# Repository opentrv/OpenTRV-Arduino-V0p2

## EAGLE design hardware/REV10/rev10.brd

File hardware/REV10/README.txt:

REV 10 is RFM23B and phototransistor and TMP112 and GSM card and optional mains power and optional relay.
Dual purpose for temp sensor deployment and as a general dumb sensor radio relay over GSM.

See requirements doc: https://docs.google.com/document/d/1RM6_tcC0Uajx6D2YfQV9GoQAOvQpk6TpT7khfn3ezBs/edit?usp=sharing

Note ITEADstudio .dru and .cam files downloaded from their site AND NOT COVERED BY OUR APACHE LICENCE
though ITEADstudio would probably be happy for you to use their service like we did!

Component-ordering document: https://docs.google.com/spreadsheets/d/10yWM68cfkmaEVJMniHg1qRwaJqgsrZ1O5jhQIcJ3FMg/edit#gid=0

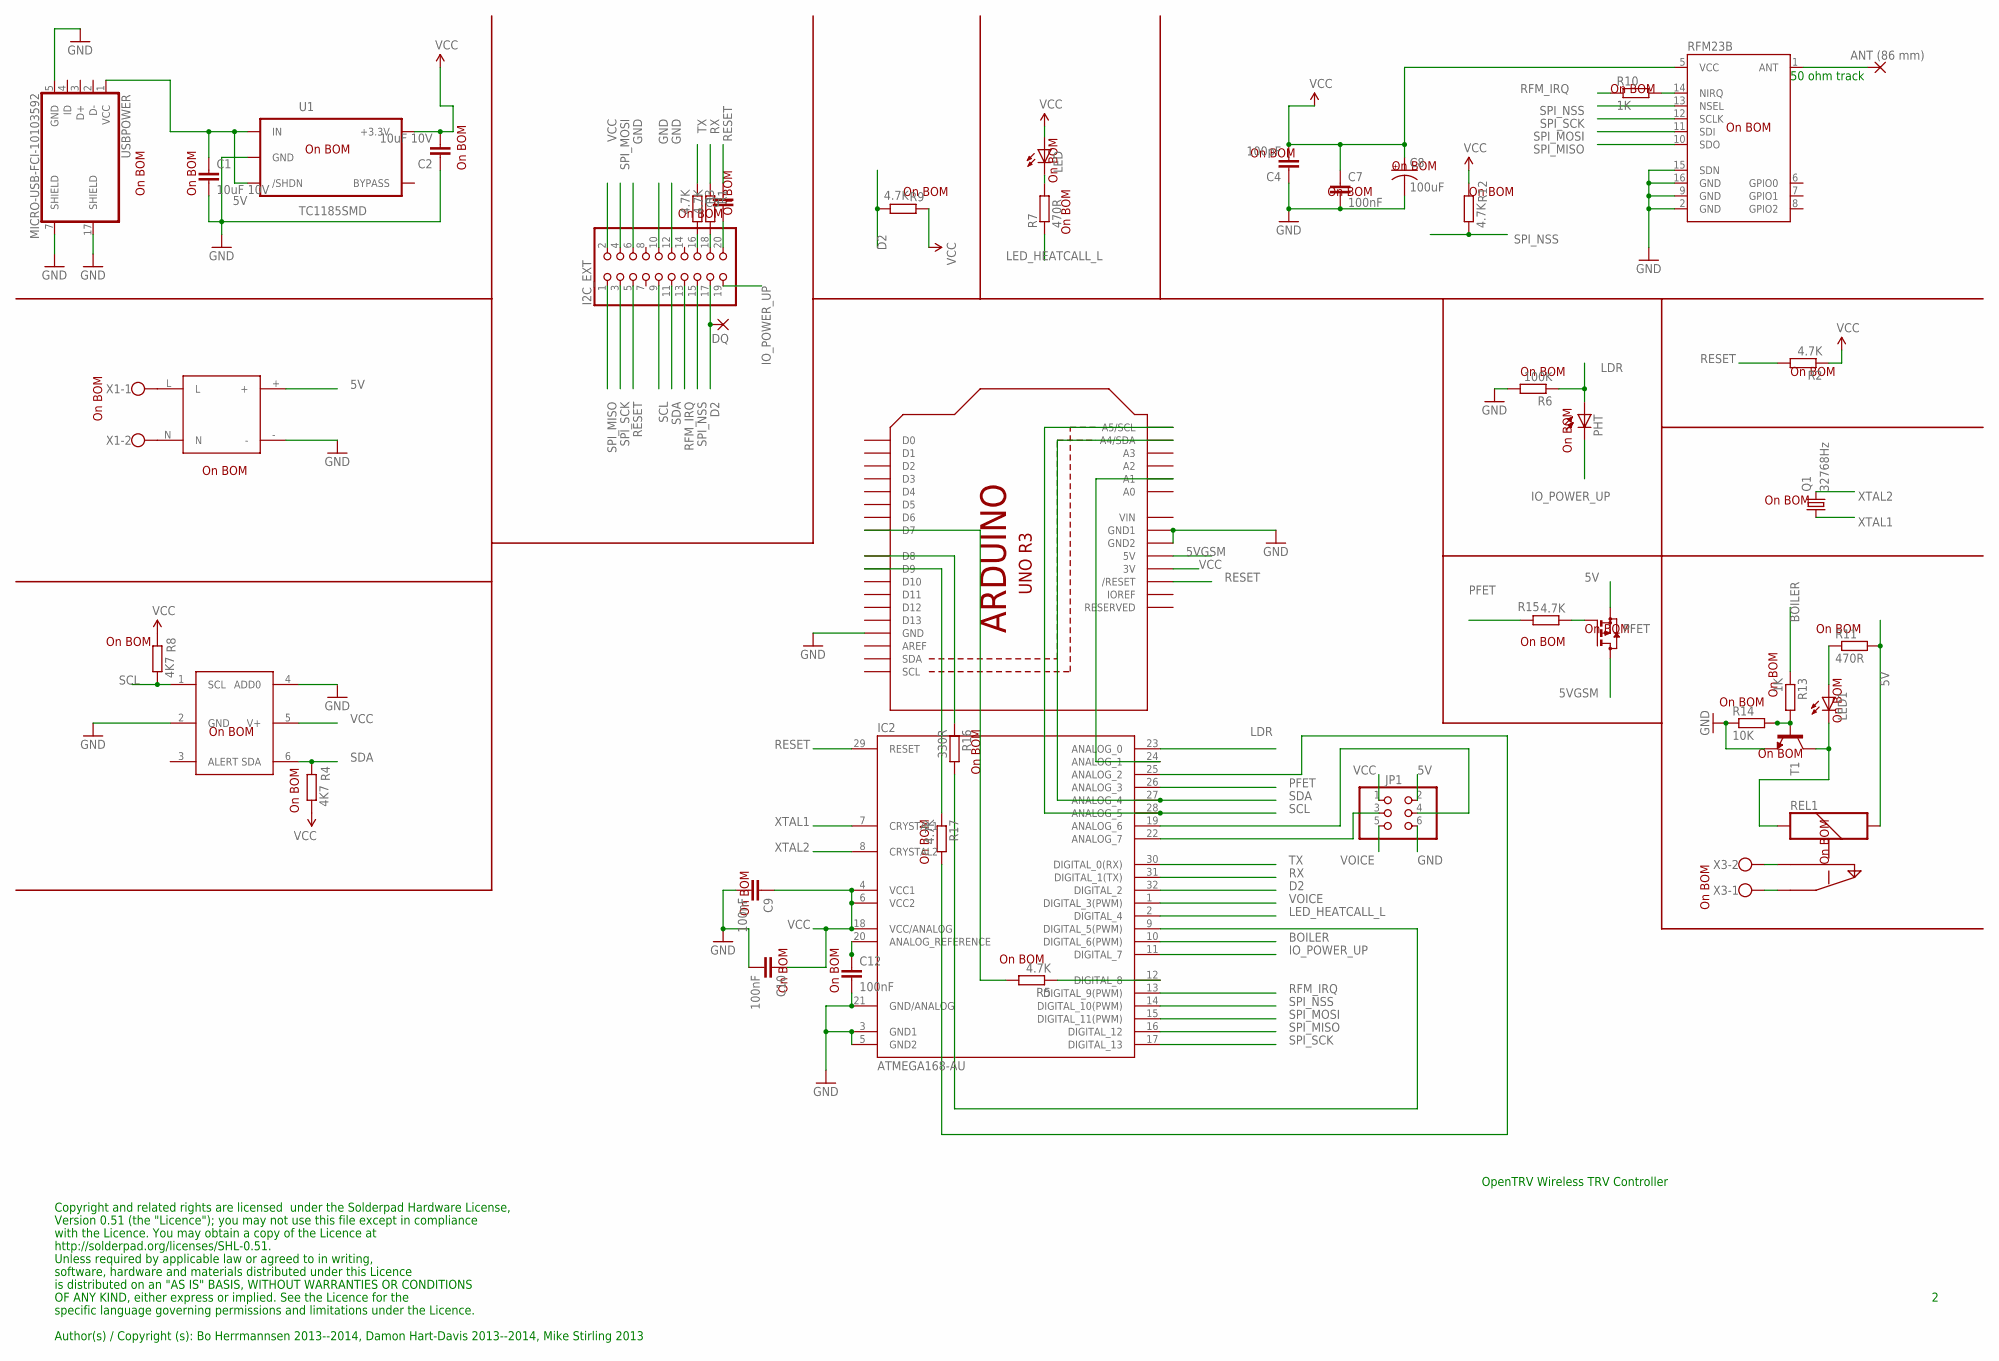
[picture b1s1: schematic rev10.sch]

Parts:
ANT1: ANT (86 mm); 2,15/1,0
C1, C2: 10uF 10V; C0603
C4: 100pF; C0603
C5, C7, C9, C10, C12: 100nF; C0603
C8: 100uF; EIA3216
DQ: 2,15/1,0
I2C_EXT: PINHD-2X10; 2X10
IC2: ATMEGA168-AU; TQFP32-08
JP1: PINHD-2X3; 2X03
LED, LED1: LEDCHIP-LED0603; CHIP-LED0603
PFET: BSS84; SOT23
PHT: BPX65
PSU: VTX-214-010-205
Q1: 32768Hz; MC-306
R1, R2, R3, R5, R9, R12, R15, R17: 4.7K; R0603
R4, R8: 4K7; R0603
R6: 100K; R0603
R7, R11: 470R; R0603
R10, R13: 1K; R0603
R14: 10K; R0603
R16: 330R; R0603
REL1: OJE-SS-103HM
RFM23B: RFM23B; RFM23-XXX-S1
T1: -NPN-SOT23-EBC; SOT23-EBC
TMP112: TMP1; TMP112
U1: TC1185SMD; TC1185
U$3: ARDUINO
USBPOWER: MICRO-USB-FCI-10103592
X1, X3: W237-102

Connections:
5V: C1.1, JP1.2, PFET.2 (S), PSU.+, R11.2, REL1.S2, U1.1 (IN), U1.3 (/SHDN), USBPOWER.1 (VCC)
5VGSM: PFET.3 (D), U$3.5V
BOILER: IC2.10 (DIGITAL_6(PWM)), R13.1
D2: DQ.1, I2C_EXT.17, IC2.32 (DIGITAL_2), R9.1
GND: C1.2, C2.1, C4.1, C7.2, C8.C (-), C9.2, C10.2, C12.2, I2C_EXT.6, I2C_EXT.10, I2C_EXT.12, IC2.3 (GND1), IC2.5 (GND2), IC2.21 (GND/ANALOG), JP1.6, PSU.-, R6.2, R14.1, RFM23B.2 (GND), RFM23B.9 (GND), RFM23B.15 (SDN), RFM23B.16 (GND), T1.E, TMP112.2 (GND), TMP112.4 (ADD0), U1.2 (GND), U$3.GND, U$3.GND1, U$3.GND2, USBPOWER.5 (GND), USBPOWER.7 (SHIELD), USBPOWER.17 (SHIELD)
IO_POWER_UP: I2C_EXT.19, IC2.11 (DIGITAL_7), PHT.K (C)
LDR: IC2.23 (ANALOG_0), PHT.A, R6.1
LED_HEATCALL_L: IC2.2 (DIGITAL_4), R7.1
unnamed: IC2.19 (ANALOG_6), JP1.4
unnamed: IC2.12 (DIGITAL_8), R5.1
unnamed: PSU.N, X1.2
unnamed: IC2.22 (ANALOG_7), JP1.3
unnamed: C12.1, IC2.20 (ANALOG_REFERENCE)
unnamed: R10.2, RFM23B.14 (NIRQ)
unnamed: PSU.L, X1.1
unnamed: IC2.25 (ANALOG_2), R17.2
unnamed: R13.2, R14.2, T1.B
unnamed: LED.C, R7.2
unnamed: LED1.C, REL1.S1, T1.C
unnamed: IC2.24 (ANALOG_1), U$3.A1
unnamed: LED1.A, R11.1
unnamed: PFET.1 (G), R15.1
unnamed: R5.2, U$3.D7
unnamed: IC2.9 (DIGITAL_5(PWM)), R16.2
unnamed: REL1.C, X3.1
unnamed: REL1.S, X3.2
unnamed: I2C_EXT.18, R1.2
unnamed: I2C_EXT.16, R3.2
unnamed: C5.2, I2C_EXT.20
unnamed: R17.1, U$3.D9
unnamed: ANT1.1, RFM23B.1 (ANT)
unnamed: R16.1, U$3.D8
PFET: IC2.26 (ANALOG_3), R15.2
RESET: C5.1, I2C_EXT.5, IC2.29 (RESET), R2.2, U$3.RESET (/RESET)
RFM_IRQ: I2C_EXT.13, IC2.13 (DIGITAL_9(PWM)), R10.1
RX: IC2.31 (DIGITAL_1(TX)), R1.1
SCL: I2C_EXT.9, IC2.28 (ANALOG_5), R8.1, TMP112.1 (SCL), U$3.A5 (A5/SCL)
SDA: I2C_EXT.11, IC2.27 (ANALOG_4), R4.2, TMP112.6 (SDA), U$3.A4 (A4/SDA)
SPI_MISO: I2C_EXT.1, IC2.16 (DIGITAL_12), RFM23B.10 (SDO)
SPI_MOSI: I2C_EXT.4, IC2.15 (DIGITAL_11(PWM)), RFM23B.11 (SDI)
SPI_NSS: I2C_EXT.15, IC2.14 (DIGITAL_10(PWM)), R12.1, RFM23B.13 (NSEL)
SPI_SCK: I2C_EXT.3, IC2.17 (DIGITAL_13), RFM23B.12 (SCLK)
TX: IC2.30 (DIGITAL_0(RX)), R3.1
VCC: C2.2, C4.2, C7.1, C8.A (+), C9.1, C10.1, I2C_EXT.2, IC2.4 (VCC1), IC2.6 (VCC2), IC2.18 (VCC/ANALOG), JP1.1, LED.A, R2.1, R4.1, R8.2, R9.2, R12.2, RFM23B.5 (VCC), TMP112.5 (V+), U1.5 (+3.3V), U$3.3V
VIN: U$3.VIN
VOICE: IC2.1 (DIGITAL_3(PWM)), JP1.5
XTAL1: IC2.7 (CRYSTAL1), Q1.1
XTAL2: IC2.8 (CRYSTAL2), Q1.4 (2)

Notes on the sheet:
Copyright and related rights are licensed under the Solderpad Hardware License,
Version 0.51 (the "Licence"); you may not use this file except in compliance
with the Licence. You may obtain a copy of the Licence at
http://solderpad.org/licenses/SHL-0.51.
Unless required by applicable law or agreed to in writing,
software, hardware and materials distributed under this Licence
is distributed on an "AS IS" BASIS, WITHOUT WARRANTIES OR CONDITIONS
Author(s) / Copyright (s): Bo Herrmannsen 2013--2014, Damon Hart-Davis 2013--2014, Mike Stirling 2013
OpenTRV Wireless TRV Controller
OF ANY KIND, either express or implied. See the Licence for the
specific language governing permissions and limitations under the Licence.
50 ohm track
On BOM

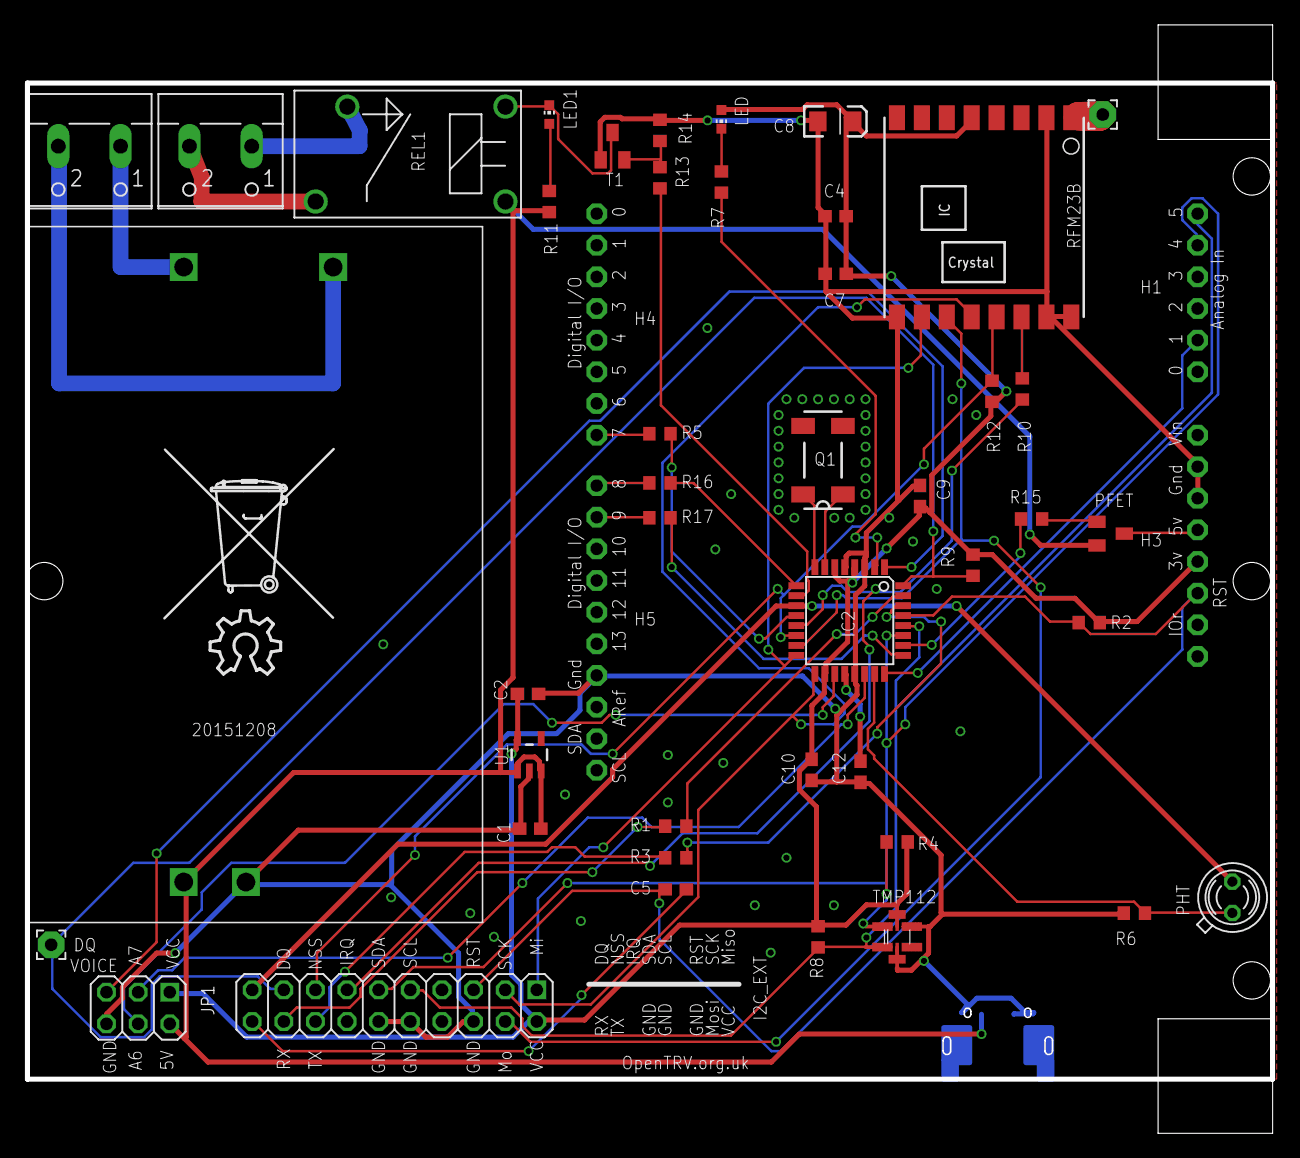
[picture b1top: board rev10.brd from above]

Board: 2 copper layers, 100.0 x 80.0 mm, 48 parts (1 on the bottom side), 47 nets.

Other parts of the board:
U$1: OSHW_10X200_NOTEXT
U$2: TONNE

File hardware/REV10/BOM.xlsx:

# of boards ttl | 100.0 |  |  | GREEN MEANS OK | RED MEANS OUT OF STOCK
Quantity per board | Need to order | Min order | Unit price | Line Total | Seller Stock No | Manufacturer | Manufacturer Part. No. | Description | Legend | Supplier | Direct Link
1.0 | 100 | 5.0 | 0.342 | 34.2 | 714-2334 | FCI | 10103592-0001LF | Micro USB socket | USBPOWER | RS Components | http://uk.rs-online.com/web/p/micro-usb-connectors/7142334/
1.0 | 100 | 10.0 | 0.241 | 24.1 | 628-3661 | Microchip | TC1185-3.3VCT713 | 3.3V Regulator | U1 | RS Components | http://uk.rs-online.com/web/p/low-dropout-voltage-regulators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
2.0 | 200 | 50.0 | 0.103 | 20.6 | 741-4434 | TDK | C1608X5R0J106M080AB | 10 uF | C1, C2 | RS Components | http://uk.rs-online.com/web/p/ceramic-multilayer-capacitors/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
1.0 | 100 | 50.0 | 0.027 | 2.7 | 213-2531 | TE Connectivity | CRG0603F100K | 100Kohm | R6 | RS Components | http://uk.rs-online.com/web/p/surface-mount-fixed-resistors/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
10.0 | 1000 | 50.0 | 0.028 | 28 | 213-2367 | TE Connectivity | CRG0603F4K7 | 4.7Kohm | R4, R8, R1, R3, R9, R12, R2, R17, R5, R15 | RS Components | http://uk.rs-online.com/web/p/surface-mount-fixed-resistors/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
2.0 | 200 | 50.0 | 0.028 | 5.6 | 213-2222 | TE Connectivity | CRG0603F470R | 470ohm | R7, R11 | RS Components | http://uk.rs-online.com/web/p/surface-mount-fixed-resistors/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
2.0 | 200 | 50.0 | 0.006 | 1.2 | 213-2266 | TE Connectivity | CRG0603F1K0 | 1Kohm | R10, R13 | RS Components | http://uk.rs-online.com/web/p/surface-mount-fixed-resistors/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
1.0 | 100 | 50.0 | 0.008 | 0.8 | 679-0226 | Vishay | CRCW0603330RFKEA | 330ohm | R16 | RS Components | http://uk.rs-online.com/web/p/surface-mount-fixed-resistors/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
1.0 | 100 | 50.0 | 0.011 | 1.1 | 213-2418 | TE Connectivity | CRG0603F10K | 10Kohm | R14 | RS Components | http://uk.rs-online.com/web/p/surface-mount-fixed-resistors/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
5.0 | 500 | 25.0 | 0.022 | 11 | 264-4630 | Kemet | C0603C104K4RAC | 100nF | C5, C9, C10, C12, C7 | RS Components | http://uk.rs-online.com/web/p/ceramic-multilayer-capacitors/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
1.0 | 100 | 50.0 | 0.026 | 2.6 | 464-6391 | AVX | 06035A101JAT2A | 100pF | C4 | RS Components | http://uk.rs-online.com/web/p/ceramic-multilayer-capacitors/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
1.0 | 100 | 10.0 | 0.215 | 21.5 | 885-1897 | Murata | GRM31CD80J107ME39L | 100uF | C8 | RS Components | http://uk.rs-online.com/web/p/ceramic-multilayer-capacitors/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
1.0 | 100 | 5.0 | 0.824 | 82.4 | 667-6120 | EPSON TOYOCOM | MC-306, 32.768kHz, 20ppm, 6pF | Crystal | Q1 | RS Components | http://uk.rs-online.com/web/p/crystal-units/6676120
1.0 | 100 | 1.0 | 1.91 | 191 | 709-8868 | Texas Instruments | TMP112AIDRLT | TMP112 | TMP112 | RS Components | http://uk.rs-online.com/web/p/temperature-humidity-sensors/7098868
2.0 | 200 | 5.0 | 0.191 | 38.2 | 1328308.0 | Vishay | TLMS1000-GS08 | LED RED | LED, LED1 | Farnell | http://uk.farnell.com/vishay/tlms1000-gs08/led-0603-red-4mcd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
1.0 | 100 | 10.0 | 0.293 | 29.3 | 700-0776 | Vishay | TEPT4400 | 60° Visible Light Phototransistor | PHT | RS Components | http://uk.rs-online.com/web/p/phototransistors/7000776/
0.001 | 0.1 | 1000.0 | 11.99 | 1.199 | 712-5320 | RS |  | 84mm* of insulated semi-flexible antenna wire (~0.33sqmm). *Depends on PCB trac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 | ANT | RS Components | http://uk.rs-online.com/web/p/hookup-equipment-wire/7125320
1.0 | 100 | 1.0 | 2.53 | 253 | 696-3092 | Atmel | ATMEGA328P-AU | ATmega328P-AU | IC1 | RS Components | http://uk.rs-online.com/web/p/microcontrollers/6963092/
1.0 | 100 | 1.0 | 3.6 | 360 | RFM23-868-S1 | HopeRF | RFM23-868-S1 | RFM23B | RFM23 | Ideetron | http://www.hoperf.nl/RFM23B
1.0 | 100 | 5.0 | 1.008 | 100.8 | 4681350.0 | Molex | 90122-0767 | Right Angle 14 Pin connector | IC2_EXT | RS Components | http://uk.rs-online.com/web/p/pcb-headers/4681350/
1.0 | 100 | 1.0 | 6.21 | 621 | 84-2192 | Vigortronix | VTX-214-010-105 | 230V AC -> 5V DC Switchmode | PSU | Rapid Online | http://www.rapidonline.com/Electrical-Power/Vigortronix-VTX-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
1.0 | 100 | 1.0 | 0.561 | 56.1 | 1891660.0 | TE Connectivity | OJE-SS-103HM,000 | Relay | Rel1 | Farnell | http://uk.farnell.com/te-connectivity-oeg/oje-ss-103hm-000/r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
1.0 | 100 | 100.0 | 0.062 | 6.2 | 827-0503 | DiodesZetex | DMP3099L-7 | PFET Sot23 | PFET | RS Components | http://uk.rs-online.com/web/p/mosfet-transistors/8270503/
1.0 | 100 | 50.0 | 0.008 | 0.8 | 445-2039 | Infineon | BC848C | NPN Sot23 | T1 | RS Components | http://uk.rs-online.com/web/p/bipolar-transistors/4452039/
2.0 | 200 | 10.0 | 0.413 | 82.6 | 710-0093 | TE Connectivity | 1546216-2 | 2 way screw terminal | X1, X3 | RS Components | http://uk.rs-online.com/web/p/pcb-terminal-blocks/7100093/
1.0 | 100 | 10.0 | 0.346 | 34.6 | 668-9485 | TE Connectivity | 826634-3 | 6 pin header | JP2 | RS Components | http://uk.rs-online.com/web/p/pcb-headers/6689485/
2.0 | 200 | 10.0 | 0.287 | 57.4 | 1593478.0 | Multicomp | 2212BR-08G | 8 pin Arduino receptacle | ?? | Farnell | http://uk.farnell.com/multicomp/2212br-08g/socket-pcb-r-a-1-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
1.0 | 100 | 10.0 | 0.561 | 56.1 | 1593462.0 | Multicomp | 2212S-06SG-85 | 6 pin Arduino receptacle | ?? | Farnell | http://uk.farnell.com/multicomp/2212s-06sg-85/socket-pcb-1-r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
1.0 | 100 | 10.0 | 0.375 | 37.5 | 7991959.0 | Harwin | M20-7821046 | 10 pin Arduino receptacle | ?? | Farnell | http://uk.farnell.com/harwin/m20-7821046/socket-pcb-0-1-10wa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
1.0 | 100 |  |  |  |  |  |  | PCB's |  | ?
1.0 | 100 |  |  |  |  |  |  | SIM900 shield |  | ? | Link??
 |  |  | Total: | 2161.599
 |  |  | Per board | 21.61599
Out of stock
1.0 | 100 | 5.0 | 0.71 | 71 | 749-2059 | Murata | GRM31CR60G107ME39L | 100uF | C8 | RS Components | http://uk.rs-online.com/web/p/ceramic-multilayer-capacitors/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
2.0 | 200 | 100.0 | 0.127 | 25.4 | 888-6029 | Lumex | SML-LX0603SIW-TR | LED RED | LED, LED1 | RS Components | http://uk.rs-online.com/web/p/visible-leds/8886029/

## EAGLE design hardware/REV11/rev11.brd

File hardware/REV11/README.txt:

REV 11 is RFM23B and phototransistor and SHT21, with no UI eg neither buttons nor LEDs.
Light-weight passive sensor, eg for baseline and general monitoring/measurement in homes.
Senses/reports: ambient light, temperature, relative humidity (plus battery voltage and restarts).
Powered by AAA cells to save space, and designed to fit into a relatively discreet small vented plastic case.

Target box: http://m.rapidonline.com/mechanical-fastenings-fixings/low-profile-sensor-case-white-30-3226

(Note: board is smaller than the maximum possible.)

Note ITEADstudio .dru and .cam files downloaded from their site AND NOT COVERED BY OUR APACHE LICENCE
though ITEADstudio would probably be happy for you to use their service like we did!

Component-ordering document: https://docs.google.com/spreadsheets/d/1gsCwtDZDTSBvkgDIGdEZPMJ3iMatSaSa38pdLNWTiDY/edit#gid=0

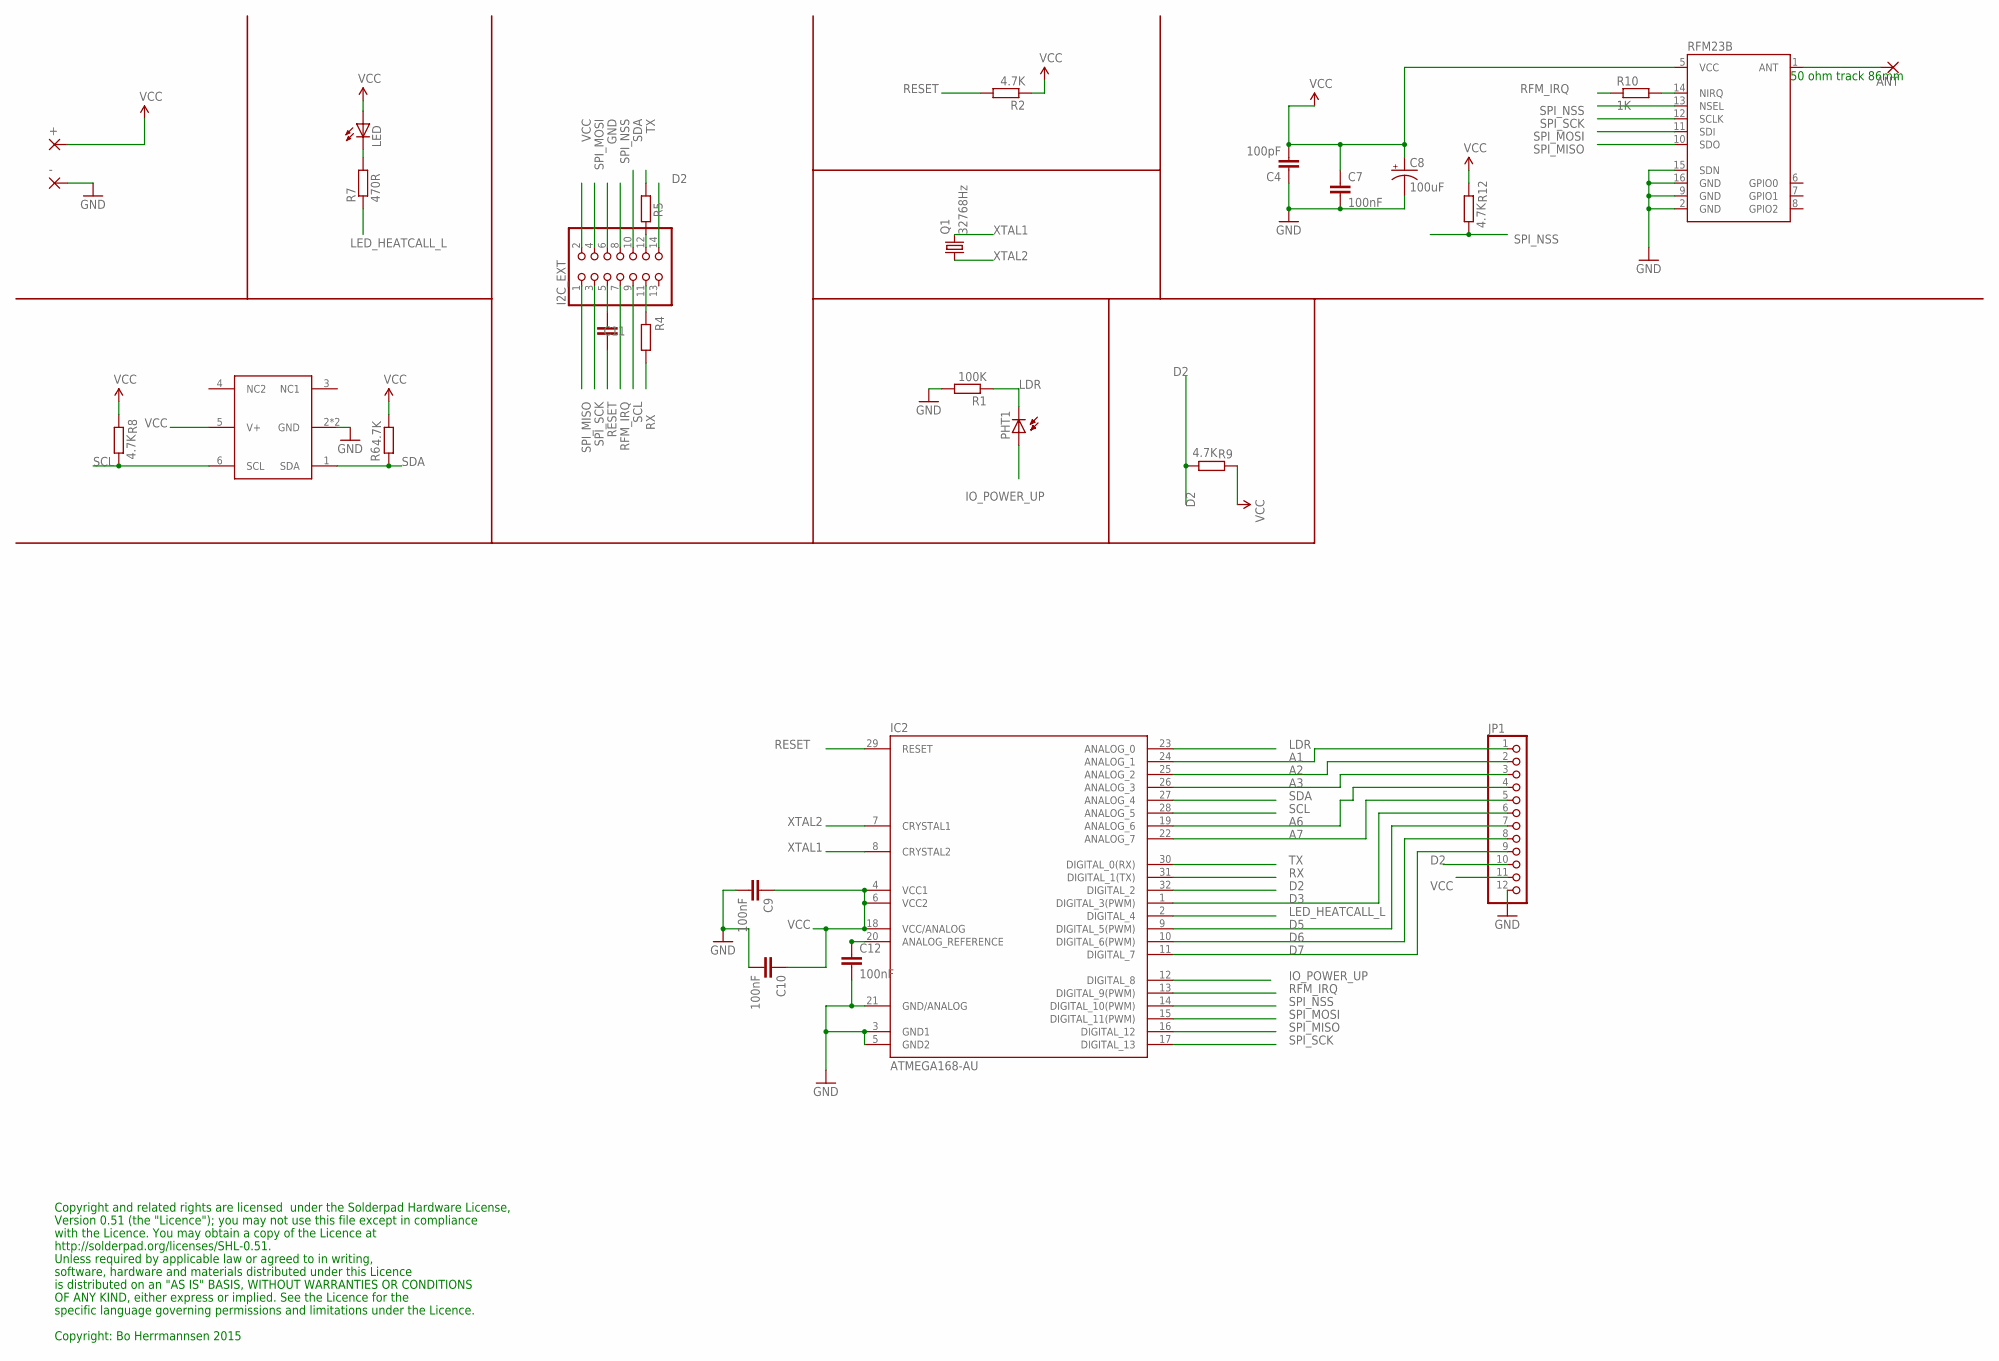
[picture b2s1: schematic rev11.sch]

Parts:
+: 2,15/1,0
-: 2,15/1,0
ANT: SMD2; SMD1,27-2,54
C4: 100pF; C0603
C7, C9, C10, C11, C12: 100nF; C0603
C8: 100uF; EIA3216
I2C_EXT: PINHD-2X7; 2X07
IC2: ATMEGA168-AU; TQFP32-08
JP1: PINHD-1X12; 1X12
LED: LEDCHIPLED_0603; CHIPLED_0603
PHT1: BPX65
Q1: 32768Hz; MC-306
R1: 100K; R0603
R2, R4, R5, R6, R8, R9, R12: 4.7K; R0603
R7: 470R; R0603
R10: 1K; R0603
RFM23B: RFM23B; RFM23-XXX-S1
U$4: SHT21

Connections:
A1: IC2.24 (ANALOG_1), JP1.1
A2: IC2.25 (ANALOG_2), JP1.2
A3: IC2.26 (ANALOG_3), JP1.3
A6: IC2.19 (ANALOG_6), JP1.4
A7: IC2.22 (ANALOG_7), JP1.5
D2: I2C_EXT.14, IC2.32 (DIGITAL_2), JP1.10, R9.1
D3: IC2.1 (DIGITAL_3(PWM)), JP1.6
D5: IC2.9 (DIGITAL_5(PWM)), JP1.7
D6: IC2.10 (DIGITAL_6(PWM)), JP1.8
D7: IC2.11 (DIGITAL_7), JP1.9
GND: -.1, C4.1, C7.2, C8.C (-), C9.2, C10.2, C12.2, I2C_EXT.6, IC2.3 (GND1), IC2.5 (GND2), IC2.21 (GND/ANALOG), JP1.12, R1.2, RFM23B.2 (GND), RFM23B.9 (GND), RFM23B.15 (SDN), RFM23B.16 (GND), U$4.2 (GND), U$4.P$1 (GND)
IO_POWER_UP: IC2.12 (DIGITAL_8), PHT1.A
LDR: IC2.23 (ANALOG_0), PHT1.K (C), R1.1
LED_HEATCALL_L: IC2.2 (DIGITAL_4), R7.1
unnamed: C11.2, I2C_EXT.5
unnamed: I2C_EXT.12, R5.2
unnamed: I2C_EXT.11, R4.2
unnamed: C12.1, IC2.20 (ANALOG_REFERENCE)
unnamed: R10.2, RFM23B.14 (NIRQ)
unnamed: LED.C, R7.2
unnamed: ANT.1, RFM23B.1 (ANT)
RESET: C11.1, IC2.29 (RESET), R2.2
RFM_IRQ: I2C_EXT.7, IC2.13 (DIGITAL_9(PWM)), R10.1
RX: IC2.31 (DIGITAL_1(TX)), R4.1
SCL: I2C_EXT.9, IC2.28 (ANALOG_5), R8.1, U$4.6 (SCL)
SDA: I2C_EXT.10, IC2.27 (ANALOG_4), R6.2, U$4.1 (SDA)
SPI_MISO: I2C_EXT.1, IC2.16 (DIGITAL_12), RFM23B.10 (SDO)
SPI_MOSI: I2C_EXT.4, IC2.15 (DIGITAL_11(PWM)), RFM23B.11 (SDI)
SPI_NSS: I2C_EXT.8, IC2.14 (DIGITAL_10(PWM)), R12.1, RFM23B.13 (NSEL)
SPI_SCK: I2C_EXT.3, IC2.17 (DIGITAL_13), RFM23B.12 (SCLK)
TX: IC2.30 (DIGITAL_0(RX)), R5.1
VCC: +.1, C4.2, C7.1, C8.A (+), C9.1, C10.1, I2C_EXT.2, IC2.4 (VCC1), IC2.6 (VCC2), IC2.18 (VCC/ANALOG), JP1.11, LED.A, R2.1, R6.1, R8.2, R9.2, R12.2, RFM23B.5 (VCC), U$4.5 (V+)
XTAL1: IC2.8 (CRYSTAL2), Q1.4 (2)
XTAL2: IC2.7 (CRYSTAL1), Q1.1

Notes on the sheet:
Copyright and related rights are licensed under the Solderpad Hardware License,
Version 0.51 (the "Licence"); you may not use this file except in compliance
with the Licence. You may obtain a copy of the Licence at
http://solderpad.org/licenses/SHL-0.51.
Unless required by applicable law or agreed to in writing,
software, hardware and materials distributed under this Licence
is distributed on an "AS IS" BASIS, WITHOUT WARRANTIES OR CONDITIONS
OF ANY KIND, either express or implied. See the Licence for the
specific language governing permissions and limitations under the Licence.
50 ohm track 86mm
Copyright: Bo Herrmannsen 2015

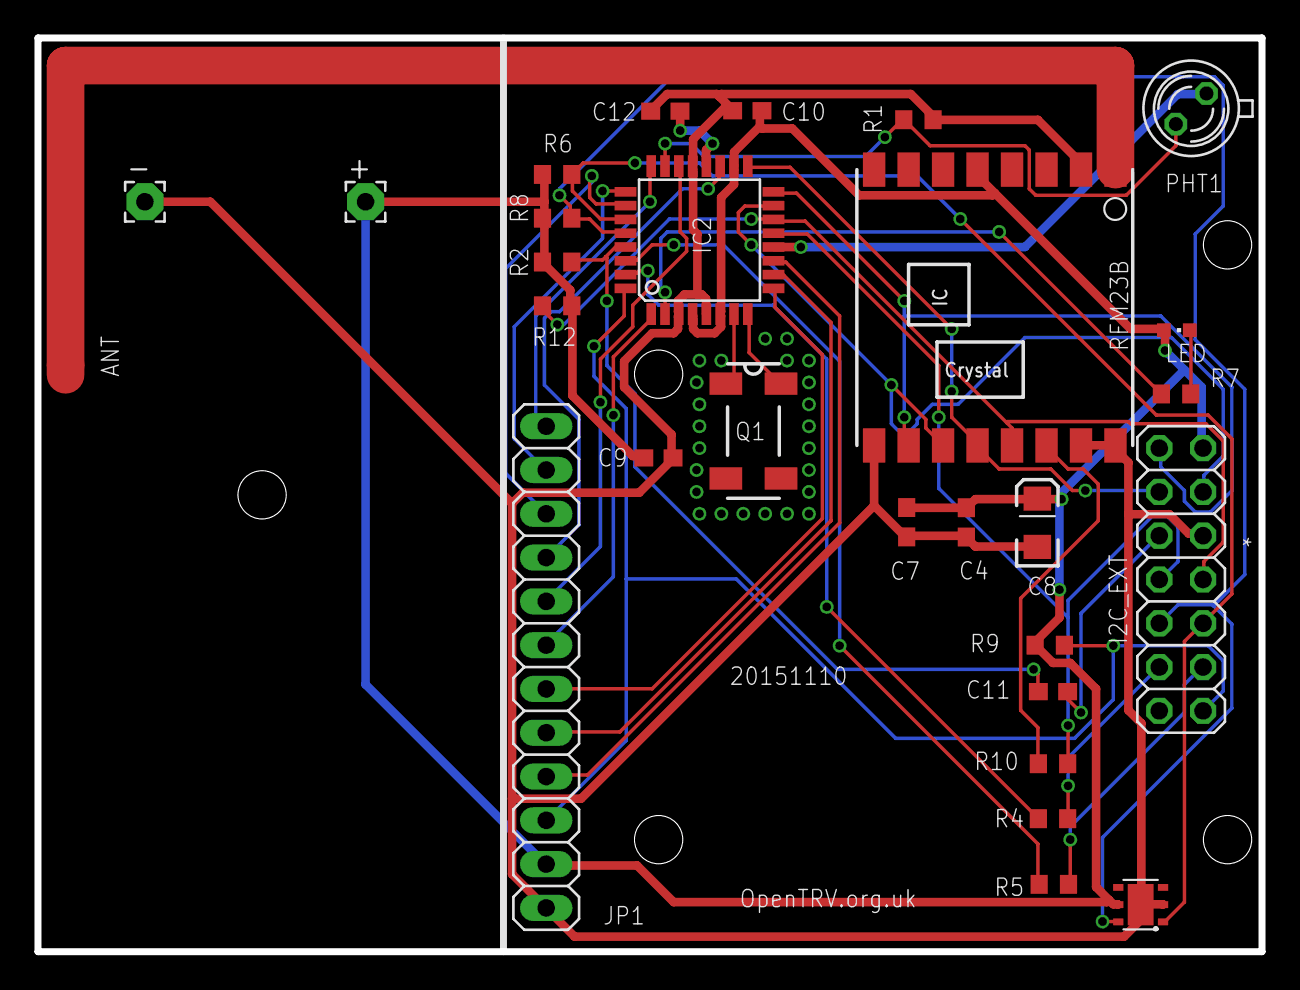
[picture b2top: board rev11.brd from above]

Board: 2 copper layers, 71.0 x 53.0 mm, 30 parts (0 on the bottom side), 34 nets.

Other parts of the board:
U$1: OSHW_10X200_NOTEXT
U$2: TONNE

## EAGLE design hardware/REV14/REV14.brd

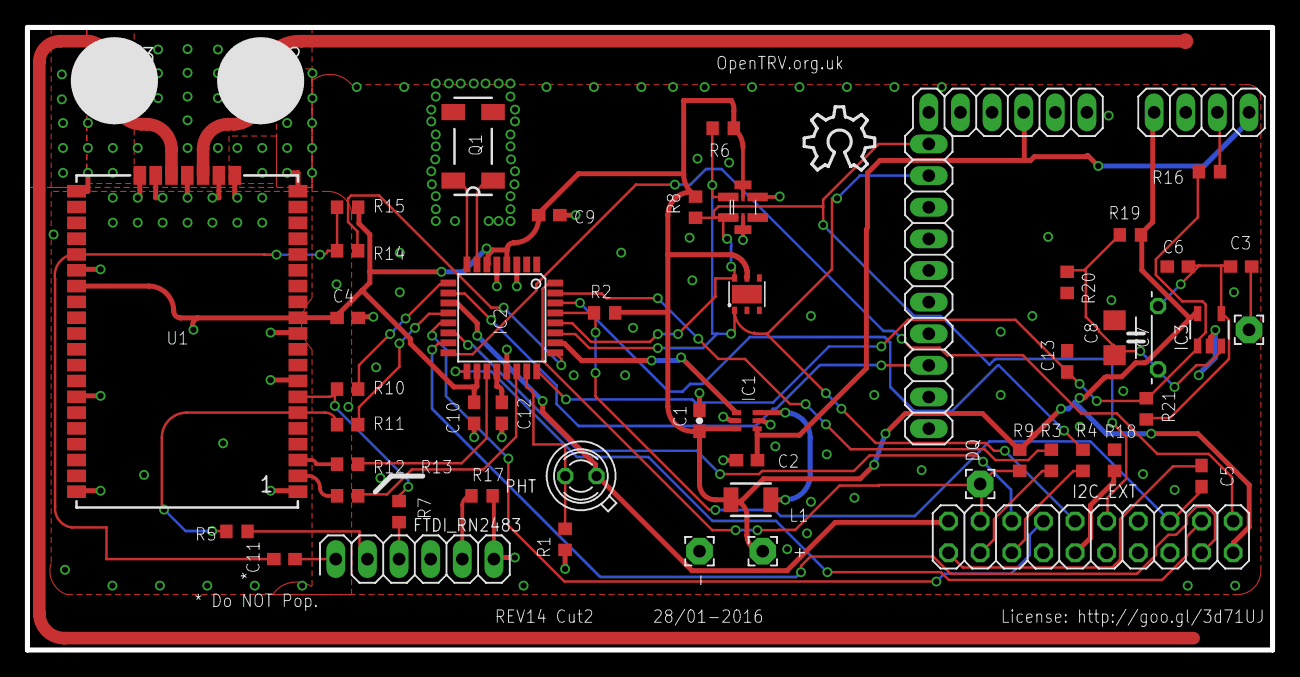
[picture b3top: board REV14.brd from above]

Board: 2 copper layers, 100.0 x 50.0 mm, 57 parts (0 on the bottom side), 47 nets.

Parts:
+: 2,15/1,0
-: 2,15/1,0
C1: 1µ; 0603-CAP
C2: 10µ; C0603
C3, C6: 22pF; C0603
C4: 100n; C0603
C5, C9, C10, C11, C12: 100nF; C0603
C7: 0.22uF; C050H075X075
C8: 100uF; C1206
C13: 0.1uF; C0603
DQ: 2,15/1,0
FTDI_RN2483: 1X06
I2C_EXT: 2X10
IC1: LTC3525; SC70
IC2: ATMEGA168-AU; TQFP32-08
IC3: TS1003IG5TMF; TS1003IG5T
JP2: 1X10
JP3: 1X06
JP4: 1X04
L1: 10 µH; 1210
PAD1, PAD2, PAD3: 2,15/1,0
PHT: BPX65
Q1: 32768Hz; MC-306
R1, R20: 100K; R0603
R2, R3, R4, R5, R6, R7, R8, R9, R10, R11, R12, R13, R14, R15, R16, R17, R18: 4.7K; R0603
R19, R21: 2.2M; R0603
TP1: TPB1,27; B1,27
TP3: TPSQTP07R; TP07R
U1: RN2483
U2: TMP112
U$1: OSHW_10X200_NOTEXT
U$4: SHT21

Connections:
CHG_PUMP: IC1.1, IC2.26
D2: DQ.1, I2C_EXT.17, IC2.32, R9.1
GND: -.1, C1.2, C2.2, C4.2, C6.2, C8.2, C9.2, C10.2, C12.2, C13.2, FTDI_RN2483.1, I2C_EXT.6, I2C_EXT.10, IC1.2, IC1.5, IC2.3, IC2.5, IC2.21, IC3.2, JP3.1, JP4.3, R1.2, R17.2, R18.1, R20.2, U1.1, U1.8, U1.11, U1.20, U1.21, U1.22, U1.24, U1.26, U1.27, U1.28, U1.33, U1.41, U1.47, U2.2, U2.4, U$4.2, U$4.P$1
IO_POWER_UP: I2C_EXT.19, IC2.11, PHT.A
LDR: IC2.23, PHT.K, R1.1
unnamed: I2C_EXT.18, R3.2
unnamed: C11.2, FTDI_RN2483.6
unnamed: I2C_EXT.16, R4.2
unnamed: C5.2, I2C_EXT.20
unnamed: FTDI_RN2483.4, R7.2
unnamed: C12.1, IC2.20
unnamed: FTDI_RN2483.5, R5.2
unnamed: IC2.9, R10.2
unnamed: IC2.12, R11.2
unnamed: IC1.6, L1.2
unnamed: IC2.19, R12.2
unnamed: IC2.22, R13.2
unnamed: IC2.25, R14.2
unnamed: FTDI_RN2483.2, R17.1
unnamed: JP4.2, R16.1
unnamed: I2C_EXT.12, R18.2
unnamed: C3.1, PAD1.1
unnamed: C3.2, C6.1, C7.2, IC3.4, R21.1
unnamed: C7.1, C8.1, IC3.3, R19.2, R20.1
unnamed: PAD2.1, TP1.TP, U1.23
unnamed: PAD3.1, TP3.TP, U1.25
PHONE: C13.1, IC2.24, IC3.1, R16.2, R21.2
RESET: C5.1, I2C_EXT.5, IC2.29, R2.2
RFM_IRQ: I2C_EXT.13, IC2.13
RN2483_RESET: C11.1, R14.1, R15.2, U1.32
RN2483_UART_CTS: R12.1, U1.3
RN2483_UART_RTS: R13.1, U1.2
RN2483_UART_RX: R7.1, R10.1, U1.7
RN2483_UART_TX: R5.1, R11.1, U1.6
RX: IC2.31, R3.1
SCL: I2C_EXT.9, IC2.28, JP2.1, R8.1, U2.1, U$4.6
SDA: I2C_EXT.11, IC2.27, JP2.2, R6.2, U2.6, U$4.1
SPI_MISO: I2C_EXT.1, IC2.16
SPI_MOSI: I2C_EXT.4, IC2.15
SPI_NSS: I2C_EXT.15, IC2.14
SPI_SCK: I2C_EXT.3, IC2.17
TX: IC2.30, R4.1
VCC: +.1, C1.1, C4.1, C9.1, C10.1, I2C_EXT.2, IC1.3, IC2.4, IC2.6, IC2.18, IC3.5, JP4.4, L1.1, R2.1, R6.1, R8.2, R9.2, R15.1, R19.1, U1.12, U1.34, U2.5, U$4.5
VCC1: C2.1, IC1.4, JP3.3, JP4.1
VOICE_NIRQ: IC2.10, JP2.8
XTAL1: IC2.8, Q1.4
XTAL2: IC2.7, Q1.1

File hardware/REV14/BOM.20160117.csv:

,,,,,,,,,,,
,,,,,,,,,,,
,,,,,,,,,,,
Quantity per board,Need to order,Min order,Unit price,Line Total,Seller Stock No,Manufacturer,Manufacturer Part. No.,Description,Legend,Supplier,Direct Link
1,0,50,0.027,0.00,213-2531,TE Connectivity,CRG0603F100K,100Kohm,R1,RS Components,http://uk.rs-online.com/web/p/surface-mount-fixed-resistors/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
10,0,50,0.009,0.00,213-2367,TE Connectivity,CRG0603F4K7,4.7Kohm,"R9, R3, R4, R18, R6, R8, R2, R5, R7, R17, R15, R10, R11, R12, R13, R14, R16",RS Components,http://uk.rs-online.com/web/p/surface-mount-fixed-resistors/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
5,0,25,0.016,0.00,264-4630,Kemet,C0603C104K4RAC,100nF,"C5, C4, (C11), C9, C10, C12",RS Components,http://uk.rs-online.com/web/p/ceramic-multilayer-capacitors/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
1,0,5,0.766,0.00,667-6120,EPSON TOYOCOM,"MC-306, 32.768kHz, 20ppm, 6pF",Crystal,Q1,RS Components,http://uk.rs-online.com/web/p/crystal-units/6676120
1,0,10,0.277,0.00,700-0776,Vishay,TEPT4400,60° Visible Light Phototransistor,PHT,RS Components,http://uk.rs-online.com/web/p/phototransistors/7000776/
1,0,1,2.260,0.00,696-3092,Atmel,ATMEGA328P-AU,ATmega328P-AU,IC2,RS Components,http://uk.rs-online.com/web/p/microcontrollers/6963092/
1,0,25,0.535,0.00,251-8165,RS,W82120T3825RC,20 pin header,IC2_EXT,Rs Components,http://uk.rs-online.com/web/p/pcb-headers/2518165/
1,0,1,3.190,0.00,30-3120,,,Box,,,http://evatron.com/enclosures/high-spec-ul94-v-0-ip-rated-en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
1,30,1,2.820,84.6,1855468,Sensiron,SHT21,SHT21,U4,RS Components,http://uk.rs-online.com/web/p/temperature-humidity-sensors/7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
1,0,1,1.770,0.00,709-8868,Texas Instruments,TMP112AIDRLT,TMP112,TMP112,RS Components,http://uk.rs-online.com/web/p/temperature-humidity-sensors/7098868
1,,,Total:,0.00,,Microchip,,RN2483,U1,RS Components,http://uk.rs-online.com/web/p/wlan-modules/8806821/
1,,,Per board,#DIV/0!,,RS,W81102T3825RC,2 way pin header,JP2,RS Components,http://uk.rs-online.com/web/p/pcb-headers/2518086/
2,,,,,,RS,W81103T3825RC,3 way pin header,JP3,RS Components,http://uk.rs-online.com/web/p/pcb-headers/2518092/
1,,,,,,RS,W81104T3825RC,4 way pin header,JP4,RS Components,http://uk.rs-online.com/web/p/pcb-headers/2518115/
1,,,,,,Harwin,M20-9990646,6 way pin header,FTDI_RN2483,RS Components,http://uk.rs-online.com/web/p/pcb-headers/7457062/
1,,,,,,Linear Technology,LTC3525ESC6-3.3#TRMPBF,Charge Pump IC,IC1,RS Components,http://uk.rs-online.com/web/p/dc-dc-converters/8226828/
1,,,,,,Kemet,C0603C105K8PACTU,1uF,C1,RS Components,http://uk.rs-online.com/web/p/ceramic-multilayer-capacitors/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
1,,,,,,TDK,C1608X5R1A106K080AC,10uF,C2,RS Components,http://uk.rs-online.com/web/p/ceramic-multilayer-capacitors/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
1,,,,,,Murata,LQH32CN100K23L,10 uH Inductor,L1,RS Components,http://uk.rs-online.com/web/p/wire-wound-surface-mount-induc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
1,,,,,,RF Solutions,ANT-BEAD-868,868 Mhz bead antenna,On TP1 track near LoRa Module,RS Components,http://uk.rs-online.com/web/p/telemetry-antennas/7424444/

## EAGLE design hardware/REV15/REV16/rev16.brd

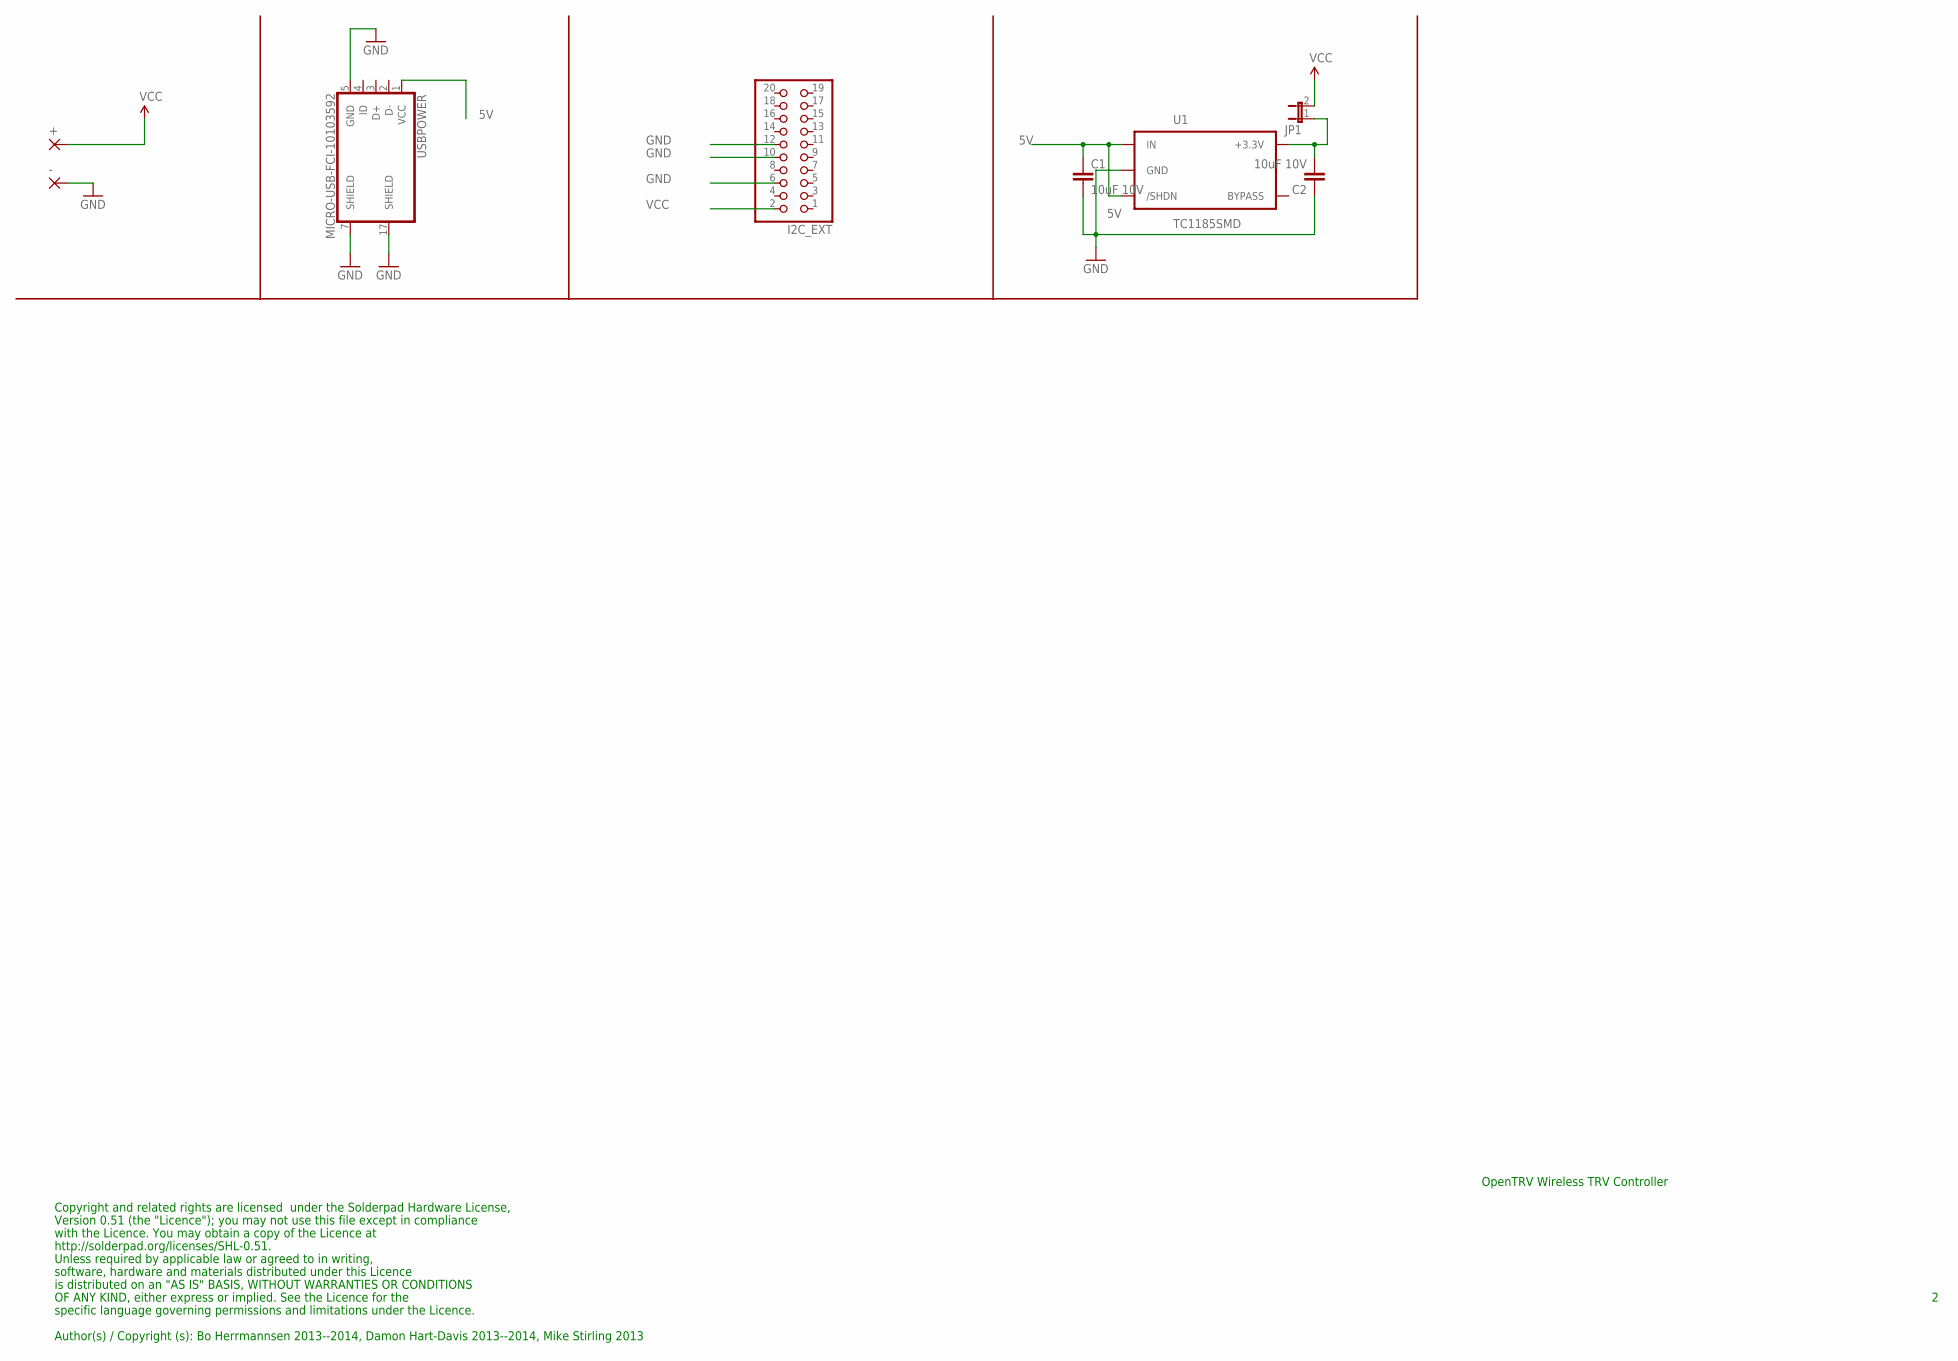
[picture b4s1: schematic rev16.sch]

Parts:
+: 2,15/1,0
-: 2,15/1,0
C1, C2: 10uF 10V; 0603-CAP
I2C_EXT: PINHD-2X10; 2X10
JP1: JP1E; JP1
U1: TC1185SMD; TC1185
USBPOWER: MICRO-USB-FCI-10103592

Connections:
5V: C1.1, U1.1 (IN), U1.3 (/SHDN), USBPOWER.1 (VCC)
GND: -.1, C1.2, C2.1, I2C_EXT.6, I2C_EXT.10, I2C_EXT.12, U1.2 (GND), USBPOWER.5 (GND), USBPOWER.7 (SHIELD), USBPOWER.17 (SHIELD)
unnamed: C2.2, JP1.1, U1.5 (+3.3V)
VCC: +.1, I2C_EXT.2, JP1.2

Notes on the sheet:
Copyright and related rights are licensed under the Solderpad Hardware License,
Version 0.51 (the "Licence"); you may not use this file except in compliance
with the Licence. You may obtain a copy of the Licence at
http://solderpad.org/licenses/SHL-0.51.
Unless required by applicable law or agreed to in writing,
software, hardware and materials distributed under this Licence
is distributed on an "AS IS" BASIS, WITHOUT WARRANTIES OR CONDITIONS
Author(s) / Copyright (s): Bo Herrmannsen 2013--2014, Damon Hart-Davis 2013--2014, Mike Stirling 2013
OpenTRV Wireless TRV Controller
OF ANY KIND, either express or implied. See the Licence for the
specific language governing permissions and limitations under the Licence.

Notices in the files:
hardware/REV10/rev10.brd:
License: http://goo.gl/3d71UJ
parts and their libraries:
SparkFun-Passives: Licensing: CC v3.0 Share-Alike You are welcome to use this library for commercial purposes.
SparkFun-Electromechanical: Licensing: Creative Commons ShareAlike 4.0 International - https://creativecommons.org/licenses/by-sa/4.0
